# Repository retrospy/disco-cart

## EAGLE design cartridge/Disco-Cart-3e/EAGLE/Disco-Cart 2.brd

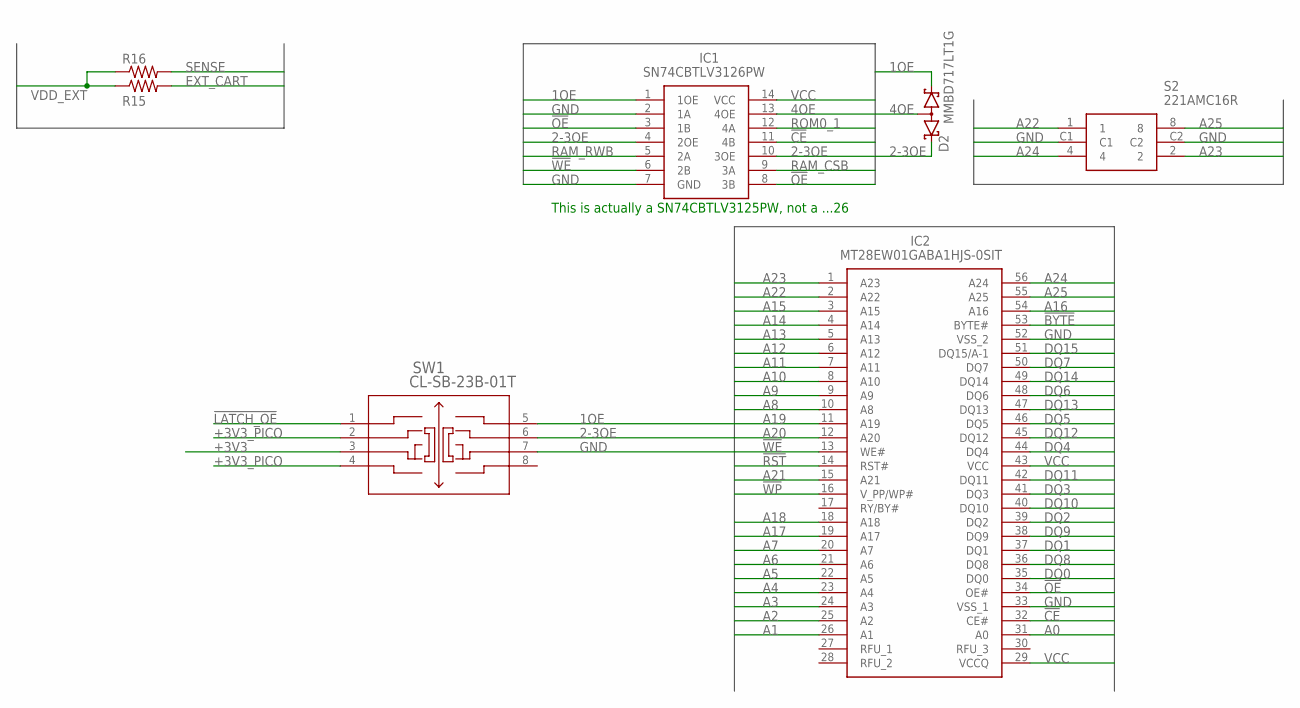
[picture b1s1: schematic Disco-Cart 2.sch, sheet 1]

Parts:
D2: MMBD717LT1G; SOT65P220X100-3N
IC1: SN74CBTLV3126PW; SOP65P640X120-14N
IC2: MT28EW01GABA1HJS-0SIT; SOP50P2000X120-56N
R15, R16: R-US_R0603; R0603
S2: 221AMC16R
SW1: CL-SB-23B-01T; CL-SB-23B_NDC

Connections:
1OE: D2.1 (K2), IC1.1 (1OE), SW1.5 (8); also elsewhere on the board
2-3OE: D2.2 (K1), IC1.4 (2OE), IC1.10 (3OE), SW1.6 (7); also elsewhere on the board
4OE: D2.3 (AA), IC1.13 (4OE); also elsewhere on the board
!BYTE: IC2.53 (BYTE#); also elsewhere on the board
!CE: IC1.11 (4B), IC2.32 (CE#); also elsewhere on the board
!LATCH_OE: SW1.1; also elsewhere on the board
!OE: IC1.3 (1B), IC1.8 (3B), IC2.34 (OE#); also elsewhere on the board
!RST: IC2.14 (RST#); also elsewhere on the board
!WE: IC1.6 (2B), IC2.13 (WE#); also elsewhere on the board
!WP: IC2.16 (V_PP/WP#); also elsewhere on the board
+3V3: SW1.3; also elsewhere on the board
+3V3_PICO: SW1.2, SW1.4; also elsewhere on the board
A0: IC2.31 (A0); also elsewhere on the board
A1: IC2.26 (A1); also elsewhere on the board
A2: IC2.25 (A2); also elsewhere on the board
A3: IC2.24 (A3); also elsewhere on the board
A4: IC2.23 (A4); also elsewhere on the board
A5: IC2.22 (A5); also elsewhere on the board
A6: IC2.21 (A6); also elsewhere on the board
A7: IC2.20 (A7); also elsewhere on the board
A8: IC2.10 (A8); also elsewhere on the board
A9: IC2.9 (A9); also elsewhere on the board
A10: IC2.8 (A10); also elsewhere on the board
A11: IC2.7 (A11); also elsewhere on the board
A12: IC2.6 (A12); also elsewhere on the board
A13: IC2.5 (A13); also elsewhere on the board
A14: IC2.4 (A14); also elsewhere on the board
A15: IC2.3 (A15); also elsewhere on the board
A16: IC2.54 (A16); also elsewhere on the board
A17: IC2.19 (A17); also elsewhere on the board
A18: IC2.18 (A18); also elsewhere on the board
A19: IC2.11 (A19); also elsewhere on the board
A20: IC2.12 (A20); also elsewhere on the board
A21: IC2.15 (A21); also elsewhere on the board
A22: IC2.2 (A22), S2.1; also elsewhere on the board
A23: IC2.1 (A23), S2.2; also elsewhere on the board
A24: IC2.56 (A24), S2.4; also elsewhere on the board
A25: IC2.55 (A25), S2.8; also elsewhere on the board
DQ0: IC2.35 (DQ0); also elsewhere on the board
DQ1: IC2.37 (DQ1); also elsewhere on the board
DQ2: IC2.39 (DQ2); also elsewhere on the board
DQ3: IC2.41 (DQ3); also elsewhere on the board
DQ4: IC2.44 (DQ4); also elsewhere on the board
DQ5: IC2.46 (DQ5); also elsewhere on the board
DQ6: IC2.48 (DQ6); also elsewhere on the board
DQ7: IC2.50 (DQ7); also elsewhere on the board
DQ8: IC2.36 (DQ8); also elsewhere on the board
DQ9: IC2.38 (DQ9); also elsewhere on the board
DQ10: IC2.40 (DQ10); also elsewhere on the board
DQ11: IC2.42 (DQ11); also elsewhere on the board
DQ12: IC2.45 (DQ12); also elsewhere on the board
DQ13: IC2.47 (DQ13); also elsewhere on the board
DQ14: IC2.49 (DQ14); also elsewhere on the board
DQ15: IC2.51 (DQ15/A-1); also elsewhere on the board
EXT_CART: R15.2; also elsewhere on the board
GND: IC1.2 (1A), IC1.7 (GND), IC2.33 (VSS_1), IC2.52 (VSS_2), S2.C1, S2.C2, SW1.7 (6); also elsewhere on the board
RAM_CSB: IC1.9 (3A); also elsewhere on the board
RAM_RWB: IC1.5 (2A); also elsewhere on the board
ROM0_1: IC1.12 (4A); also elsewhere on the board
SENSE: R16.2; also elsewhere on the board
VCC: IC1.14 (VCC), IC2.29 (VCCQ), IC2.43 (VCC); also elsewhere on the board
VDD_EXT: R15.1, R16.1; also elsewhere on the board

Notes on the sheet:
This is actually a SN74CBTLV3125PW, not a ...26

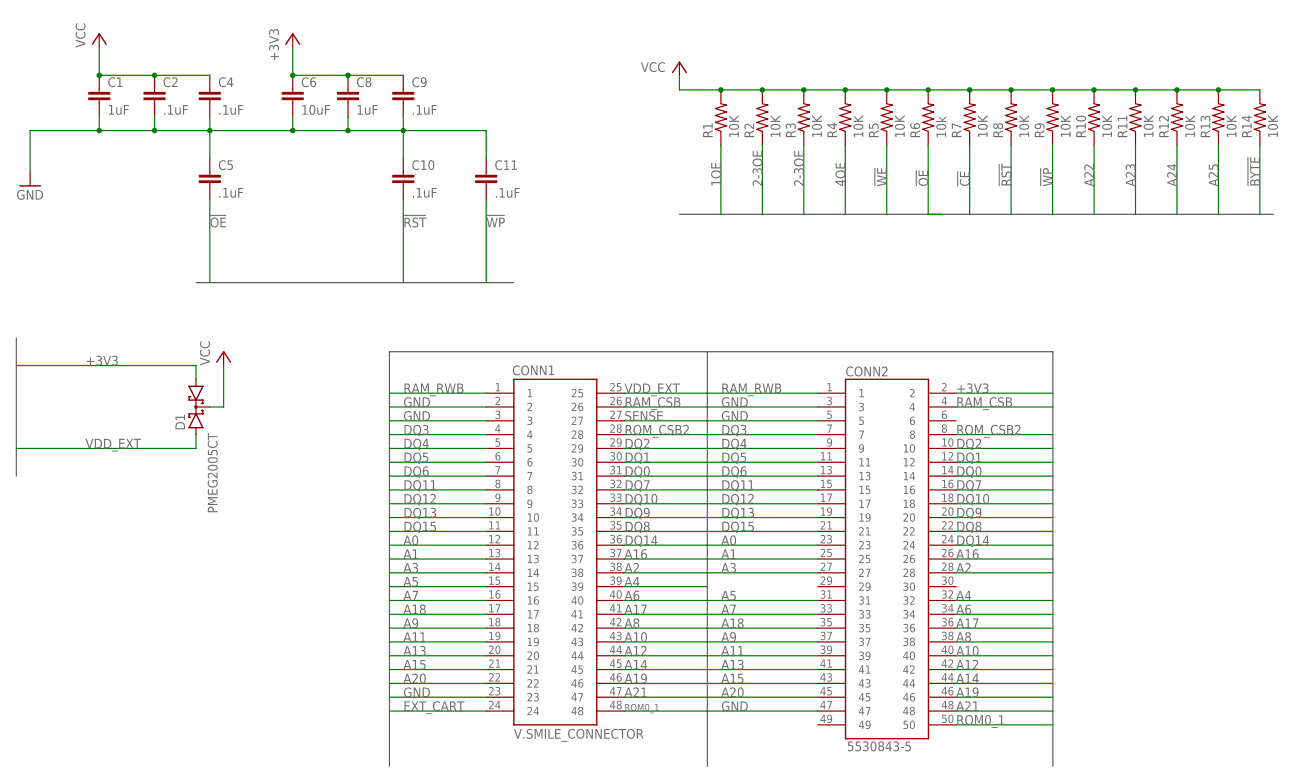
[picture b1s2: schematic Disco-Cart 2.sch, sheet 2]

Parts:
C1, C8: 1uF; C0805
C2, C4, C5, C9, C10, C11: .1uF; C0805
C6: 10uF; C0805
CONN1: V.SMILE_CONNECTOR
CONN2: 5530843-5; TE_5530843-5
D1: PMEG2005CT; SOT23
R1, R2, R3, R4, R5, R7, R8, R9, R10, R11, R12, R13, R14: 10K; M0805
R6: 10k; M0805

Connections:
1OE: R1.1; also elsewhere on the board
2-3OE: R2.1, R3.1; also elsewhere on the board
4OE: R4.1; also elsewhere on the board
!BYTE: R14.1; also elsewhere on the board
!CE: R7.1; also elsewhere on the board
!OE: C5.2, R6.1; also elsewhere on the board
!RST: C10.2, R8.1; also elsewhere on the board
!WE: R5.1; also elsewhere on the board
!WP: C11.2, R9.1; also elsewhere on the board
+3V3: C6.1, C8.1, C9.1, CONN2.2, D1.1 (A1); also elsewhere on the board
A0: CONN1.12, CONN2.23; also elsewhere on the board
A1: CONN1.13, CONN2.25; also elsewhere on the board
A2: CONN1.38, CONN2.28; also elsewhere on the board
A3: CONN1.14, CONN2.27; also elsewhere on the board
A4: CONN1.39, CONN2.32; also elsewhere on the board
A5: CONN1.15, CONN2.31; also elsewhere on the board
A6: CONN1.40, CONN2.34; also elsewhere on the board
A7: CONN1.16, CONN2.33; also elsewhere on the board
A8: CONN1.42, CONN2.38; also elsewhere on the board
A9: CONN1.18, CONN2.37; also elsewhere on the board
A10: CONN1.43, CONN2.40; also elsewhere on the board
A11: CONN1.19, CONN2.39; also elsewhere on the board
A12: CONN1.44, CONN2.42; also elsewhere on the board
A13: CONN1.20, CONN2.41; also elsewhere on the board
A14: CONN1.45, CONN2.44; also elsewhere on the board
A15: CONN1.21, CONN2.43; also elsewhere on the board
A16: CONN1.37, CONN2.26; also elsewhere on the board
A17: CONN1.41, CONN2.36; also elsewhere on the board
A18: CONN1.17, CONN2.35; also elsewhere on the board
A19: CONN1.46, CONN2.46; also elsewhere on the board
A20: CONN1.22, CONN2.45; also elsewhere on the board
A21: CONN1.47, CONN2.48; also elsewhere on the board
A22: R10.1; also elsewhere on the board
A23: R11.1; also elsewhere on the board
A24: R12.1; also elsewhere on the board
A25: R13.1; also elsewhere on the board
DQ0: CONN1.31, CONN2.14; also elsewhere on the board
DQ1: CONN1.30, CONN2.12; also elsewhere on the board
DQ2: CONN1.29, CONN2.10; also elsewhere on the board
DQ3: CONN1.4, CONN2.7; also elsewhere on the board
DQ4: CONN1.5, CONN2.9; also elsewhere on the board
DQ5: CONN1.6, CONN2.11; also elsewhere on the board
DQ6: CONN1.7, CONN2.13; also elsewhere on the board
DQ7: CONN1.32, CONN2.16; also elsewhere on the board
DQ8: CONN1.35, CONN2.22; also elsewhere on the board
DQ9: CONN1.34, CONN2.20; also elsewhere on the board
DQ10: CONN1.33, CONN2.18; also elsewhere on the board
DQ11: CONN1.8, CONN2.15; also elsewhere on the board
DQ12: CONN1.9, CONN2.17; also elsewhere on the board
DQ13: CONN1.10, CONN2.19; also elsewhere on the board
DQ14: CONN1.36, CONN2.24; also elsewhere on the board
DQ15: CONN1.11, CONN2.21; also elsewhere on the board
EXT_CART: CONN1.24; also elsewhere on the board
GND: C1.2, C2.2, C4.2, C5.1, C6.2, C8.2, C9.2, C10.1, C11.1, CONN1.2, CONN1.3, CONN1.23, CONN2.3, CONN2.5, CONN2.47; also elsewhere on the board
RAM_CSB: CONN1.26, CONN2.4; also elsewhere on the board
RAM_RWB: CONN1.1, CONN2.1; also elsewhere on the board
ROM0_1: CONN1.48, CONN2.50; also elsewhere on the board
ROM_CSB2: CONN1.28, CONN2.8; also elsewhere on the board
SENSE: CONN1.27; also elsewhere on the board
VCC: C1.1, C2.1, C4.1, D1.3 (C), R1.2, R2.2, R3.2, R4.2, R5.2, R6.2, R7.2, R8.2, R9.2, R10.2, R11.2, R12.2, R13.2, R14.2; also elsewhere on the board
VDD_EXT: CONN1.25, D1.2 (A2); also elsewhere on the board

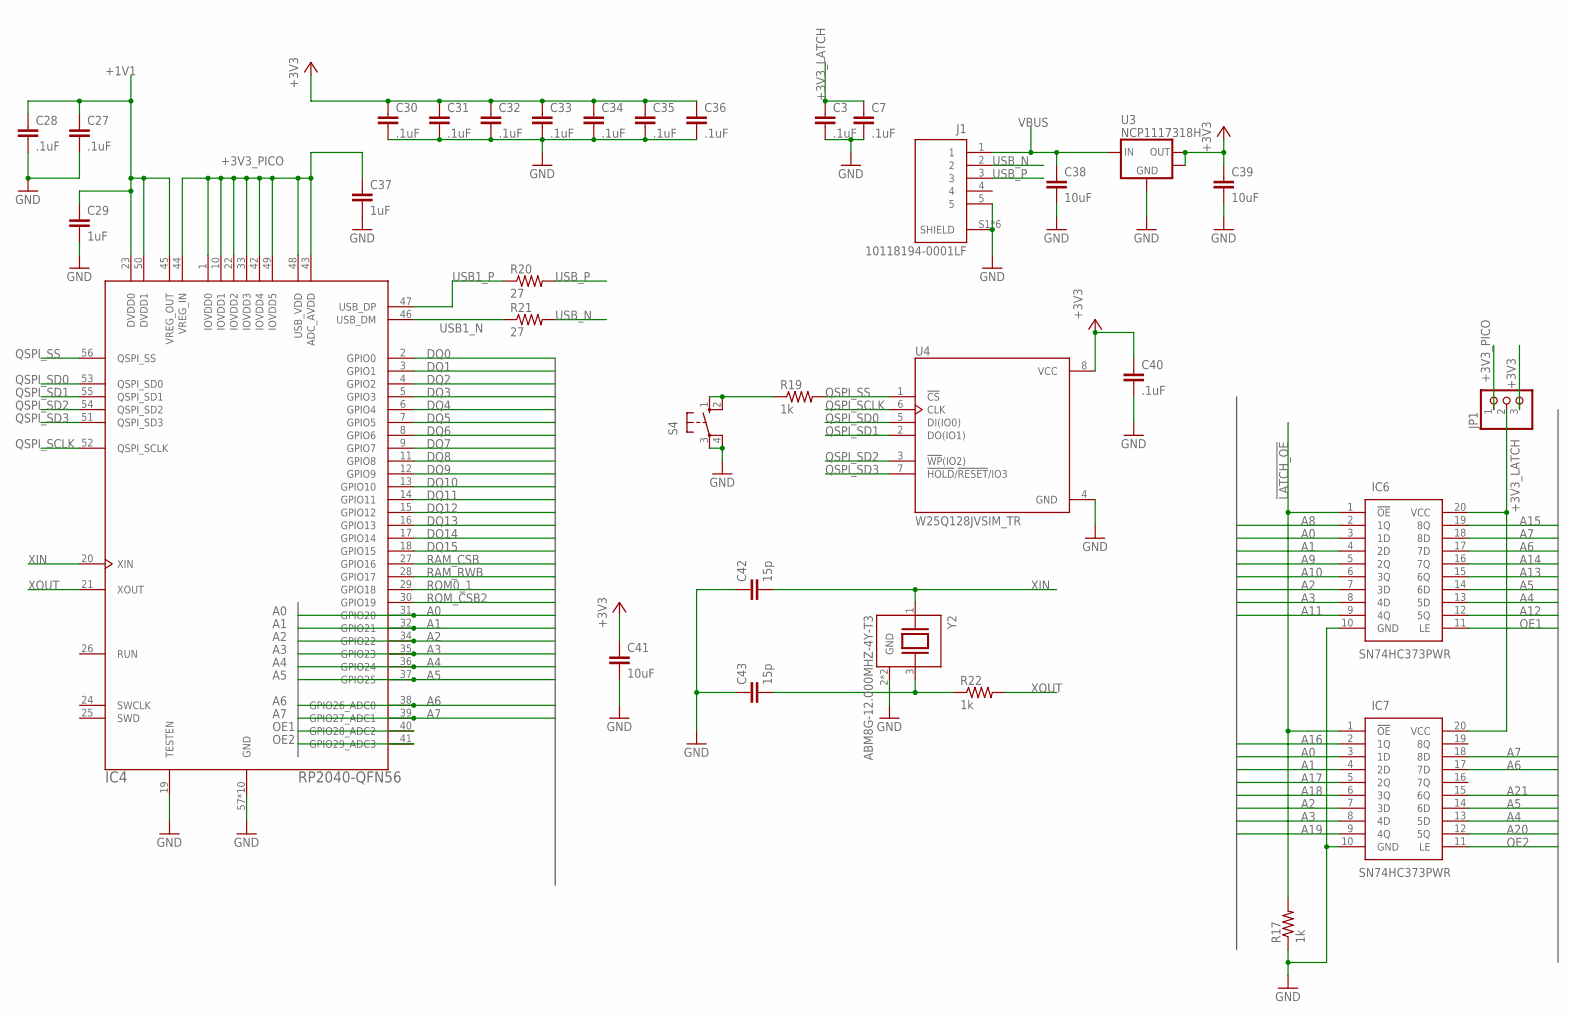
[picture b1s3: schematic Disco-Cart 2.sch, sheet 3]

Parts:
C3, C7, C27, C28, C30, C31, C32, C33, C34, C35, C36, C40: .1uF; C0402
C29, C37: 1uF; C0402
C38, C39, C41: 10uF; C0805
C42, C43: 15p; C0402
IC4: RP2040-QFN56; RP2040-QFN-56
IC6, IC7: SN74HC373PWR; SOP65P640X120-20N
J1: 10118194-0001LF; AMPHENOL_10118194-0001LF
JP1: PINHD-1X3; 1X03
R17: 1k; R0805
R19, R22: 1k; R0402
R20, R21: 27; R0402
S4: 10-XX; B3F-10XX
U3: NCP1117318H; SOT223
U4: W25Q128JVSIM_TR; SOIC127P790X216-8N
Y2: ABM8G-12.000MHZ-4Y-T3; XTAL_ABM8G-12.000MHZ-4Y-T3

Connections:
!LATCH_OE: IC6.1 (!OE), IC7.1 (!OE), R17.2; also elsewhere on the board
+1V1: C27.1, C28.1, C29.1, IC4.23 (DVDD0), IC4.45 (VREG_OUT), IC4.50 (DVDD1)
+3V3: C30.1, C31.1, C32.1, C33.1, C34.1, C35.1, C36.1, C39.1, C40.1, C41.1, JP1.3, U3.2 (OUT), U3.TAB (OUT), U4.8 (VCC); also elsewhere on the board
+3V3_LATCH: C3.1, C7.1, IC6.20 (VCC), IC7.20 (VCC), JP1.2
+3V3_PICO: C37.1, IC4.1 (IOVDD0), IC4.10 (IOVDD1), IC4.22 (IOVDD2), IC4.33 (IOVDD3), IC4.42 (IOVDD4), IC4.43 (ADC_AVDD), IC4.44 (VREG_IN), IC4.48 (USB_VDD), IC4.49 (IOVDD5), JP1.1; also elsewhere on the board
A0: IC4.31 (GPIO20), IC6.3 (1D), IC7.3 (1D); also elsewhere on the board
A1: IC4.32 (GPIO21), IC6.4 (2D), IC7.4 (2D); also elsewhere on the board
A2: IC4.34 (GPIO22), IC6.7 (3D), IC7.7 (3D); also elsewhere on the board
A3: IC4.35 (GPIO23), IC6.8 (4D), IC7.8 (4D); also elsewhere on the board
A4: IC4.36 (GPIO24), IC6.13 (5D), IC7.13 (5D); also elsewhere on the board
A5: IC4.37 (GPIO25), IC6.14 (6D), IC7.14 (6D); also elsewhere on the board
A6: IC4.38 (GPIO26_ADC0), IC6.17 (7D), IC7.17 (7D); also elsewhere on the board
A7: IC4.39 (GPIO27_ADC1), IC6.18 (8D), IC7.18 (8D); also elsewhere on the board
A8: IC6.2 (1Q); also elsewhere on the board
A9: IC6.5 (2Q); also elsewhere on the board
A10: IC6.6 (3Q); also elsewhere on the board
A11: IC6.9 (4Q); also elsewhere on the board
A12: IC6.12 (5Q); also elsewhere on the board
A13: IC6.15 (6Q); also elsewhere on the board
A14: IC6.16 (7Q); also elsewhere on the board
A15: IC6.19 (8Q); also elsewhere on the board
A16: IC7.2 (1Q); also elsewhere on the board
A17: IC7.5 (2Q); also elsewhere on the board
A18: IC7.6 (3Q); also elsewhere on the board
A19: IC7.9 (4Q); also elsewhere on the board
A20: IC7.12 (5Q); also elsewhere on the board
A21: IC7.15 (6Q); also elsewhere on the board
DQ0: IC4.2 (GPIO0); also elsewhere on the board
DQ1: IC4.3 (GPIO1); also elsewhere on the board
DQ2: IC4.4 (GPIO2); also elsewhere on the board
DQ3: IC4.5 (GPIO3); also elsewhere on the board
DQ4: IC4.6 (GPIO4); also elsewhere on the board
DQ5: IC4.7 (GPIO5); also elsewhere on the board
DQ6: IC4.8 (GPIO6); also elsewhere on the board
DQ7: IC4.9 (GPIO7); also elsewhere on the board
DQ8: IC4.11 (GPIO8); also elsewhere on the board
DQ9: IC4.12 (GPIO9); also elsewhere on the board
DQ10: IC4.13 (GPIO10); also elsewhere on the board
DQ11: IC4.14 (GPIO11); also elsewhere on the board
DQ12: IC4.15 (GPIO12); also elsewhere on the board
DQ13: IC4.16 (GPIO13); also elsewhere on the board
DQ14: IC4.17 (GPIO14); also elsewhere on the board
DQ15: IC4.18 (GPIO15); also elsewhere on the board
GND: C3.2, C7.2, C27.2, C28.2, C29.2, C30.2, C31.2, C32.2, C33.2, C34.2, C35.2, C36.2, C37.2, C38.2, C39.2, C40.2, C41.2, C42.1, C43.1, IC4.19 (TESTEN), IC4.57 (GND), IC4.58 (GND), IC4.59 (GND), IC4.60 (GND), IC4.61 (GND), IC4.62 (GND), IC4.63 (GND), IC4.64 (GND), IC4.65 (GND), IC4.66 (GND), IC6.10 (GND), IC7.10 (GND), J1.5, J1.S1 (SHIELD), J1.S2 (SHIELD), J1.S3 (SHIELD), J1.S4 (SHIELD), J1.S5 (SHIELD), J1.S6 (SHIELD), R17.1, S4.3, S4.4 (P1), U3.1 (GND), U4.4 (GND), Y2.2 (GND), Y2.4 (GND); also elsewhere on the board
unnamed: R19.1, S4.1 (S), S4.2 (S1)
OE1: IC4.40 (GPIO28_ADC2), IC6.11 (LE)
OE2: IC4.41 (GPIO29_ADC3), IC7.11 (LE)
QSPI_SCLK: IC4.52 (QSPI_SCLK), U4.6 (CLK)
QSPI_SD0: IC4.53 (QSPI_SD0), U4.5 (DI(IO0))
QSPI_SD1: IC4.55 (QSPI_SD1), U4.2 (DO(IO1))
QSPI_SD2: IC4.54 (QSPI_SD2), U4.3 (!WP!(IO2))
QSPI_SD3: IC4.51 (QSPI_SD3), U4.7 (!HOLD!/!RESET!/IO3)
QSPI_SS: IC4.56 (QSPI_SS), R19.2, U4.1 (!CS)
RAM_CSB: IC4.27 (GPIO16); also elsewhere on the board
RAM_RWB: IC4.28 (GPIO17); also elsewhere on the board
ROM0_1: IC4.29 (GPIO18); also elsewhere on the board
ROM_CSB2: IC4.30 (GPIO19); also elsewhere on the board
USB1_N: IC4.46 (USB_DM), R21.1
USB1_P: IC4.47 (USB_DP), R20.1
USB_N: J1.2, R21.2
USB_P: J1.3, R20.2
VBUS: C38.1, J1.1, U3.3 (IN)
XIN: C42.2, IC4.20 (XIN), Y2.1
XOUT: IC4.21 (XOUT), R22.2
XOUT2: C43.2, R22.1, Y2.3 (2)

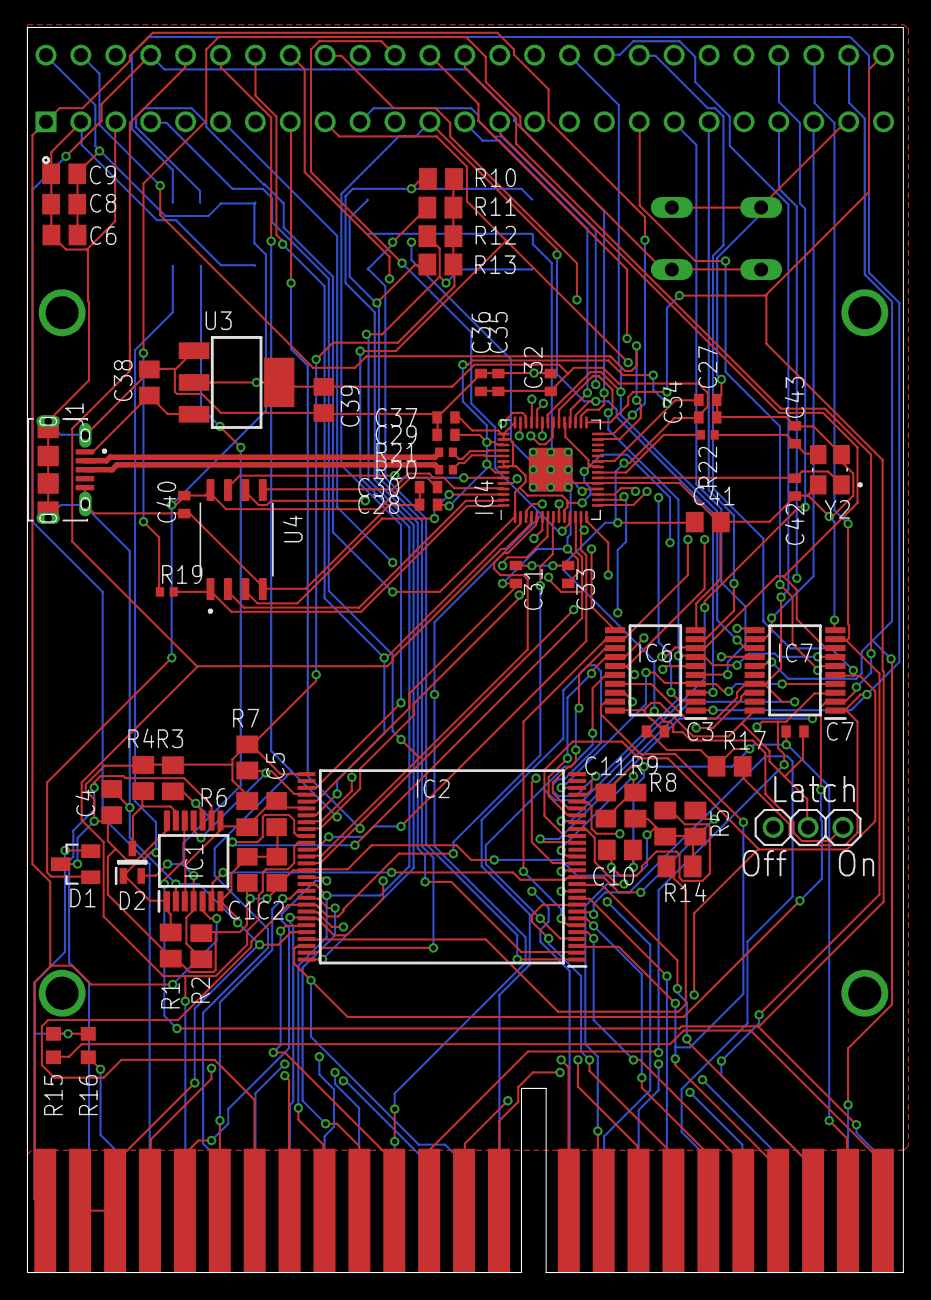
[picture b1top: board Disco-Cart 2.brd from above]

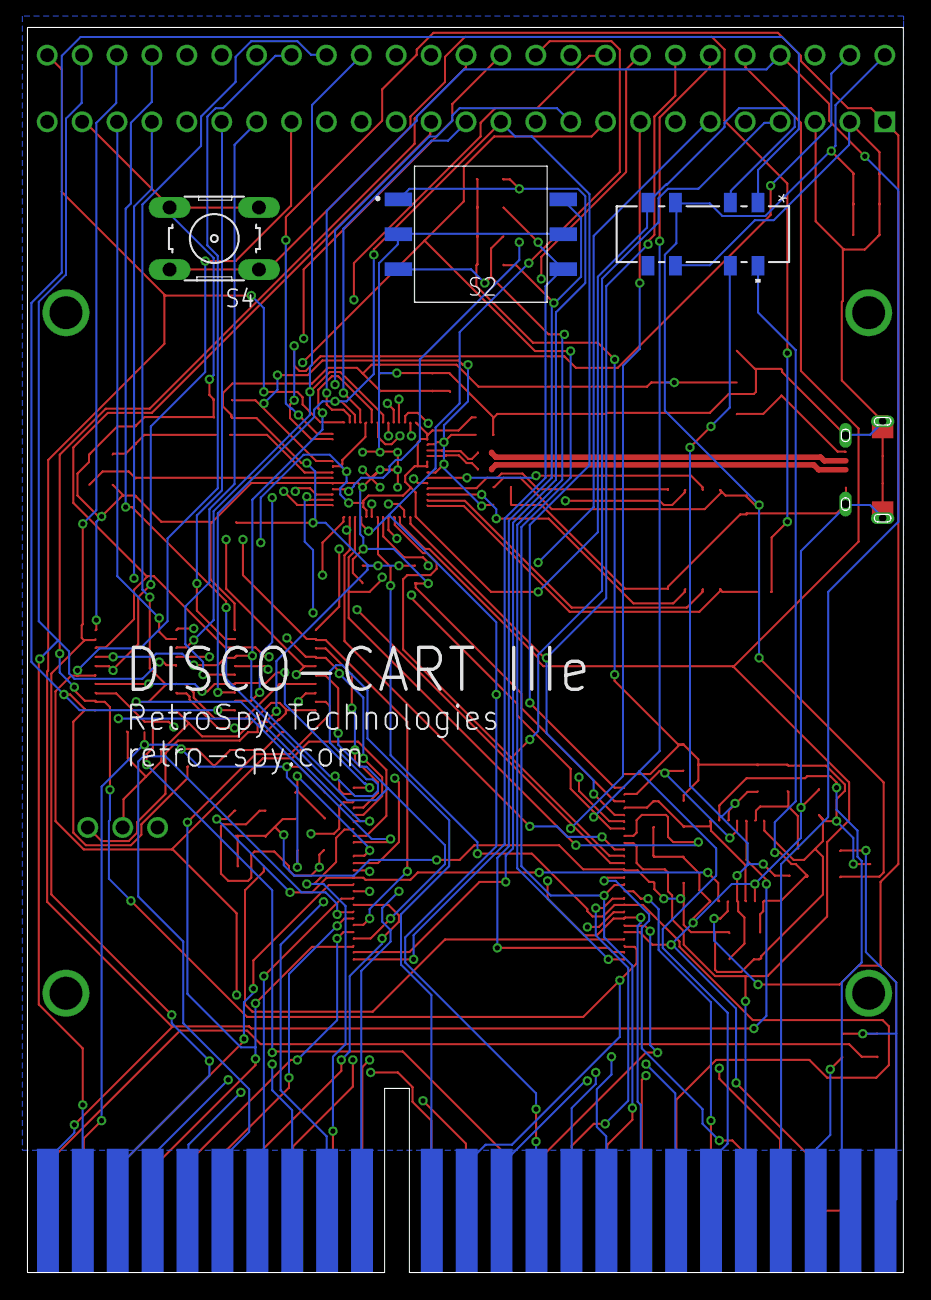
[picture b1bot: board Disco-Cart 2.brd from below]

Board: 4 copper layers, 63.7 x 90.6 mm, 66 parts (3 on the bottom side), 82 nets.

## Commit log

2023-09-15 Added BOM and centroid file
2023-09-16 1.0 of Disco-Cart Utility
2023-09-17 Added release scripts for Windows and Linux
2023-09-17 Changing permissions of linux release scripts
2023-09-17 Changed some relative paths for windows build
2023-09-17 Type in x86 build script
2023-09-17 More relative path changes in release scripts
2023-09-17 Fixed version number
2023-10-13 App actually dumps and uploads now.
2023-10-14 Fixed the "Unable to find a usable digit" error on dump
2023-10-14 fixed the "unable to find usable digit" error on read
2023-10-19 Starting up without an SD card should be ok.
2023-11-26 Moving V2 firmware and renaming DiscoCartUtil to DiscoCartV2
2023-11-29 Fixing permissions on unix release scripts
2024-02-11 Ported code to support new Mega based dumper.
2024-06-05 rp2040 prototype
2024-06-06 RP2040 V2 code complete
2024-07-10 Its slow, but it works
2024-07-10 Updated build scripts for .NET 8.0
2024-07-27 V3 works
2024-07-28 Rev IIId uploads and dumps successfully
2024-09-25 RetryCount of Dump is now configurable
2024-10-03 Re-enabled classic upload for V1 Disco-Carts
2024-10-03 Fixed dump being off by 2 bytes
2024-10-04 Uploading cartridge hardware files
2024-11-23 Adjusting Clock Speed
2025-01-15 Added simple tester and "fixed" not waiting long enough after an ERS operation
2025-01-15 Added writing to every block on each settings to tester

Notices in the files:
parts and their libraries:
COPYRIGHT: Copyright (C) 2024 Ultra Librarian. All rights reserved.
